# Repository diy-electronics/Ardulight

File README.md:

Ardulight
=========

Ardu(ino)(Ambi)light: An arduino based ambilight controller for WS2801 based digital rgb led pixels.

Example-Video:<br />

Images
------

&nbsp;&nbsp;&nbsp;

Assembly
--------

Assembly instructions including a BOM (bill of materials) can be found [here](../master/pcb).<br />
The pcb has to be soldered by hot air or by reflow due to the qfp package of the atmega32u4.

Wiring
------

For a detailed wiring guide look [here](https://learn.adafruit.com/adalight-diy-ambient-tv-lighting/wiring-1).<br />
The LED-Strip has to be powered from an external power source, using e.g. a connector like [this](https://www.adafruit.com/products/368).<br />
You only have to connect GND, CLK (SCK) and DAT (MOSI).  

Firmware
--------

The firmware can be found [here](../master/firmware/firmware.pde)<br />
You can flash this firmware using an isp-programmer.<br />
Alternatively you can first flash the arduino leonardo bootloader with an isp-programmer and then flash the firmware directly over usb since the ambilight controller is compatible with the arduino leonardo.

Software
--------

The ambilight controller works with [Prismatik from woodenshark](https://github.com/woodenshark/Lightpack/releases/latest) (Alternative download [here](http://lightpack.tv/downloads)).

To fix the systems device name and permissions for Ardulight on linux systems, you can add [the udev rule](98-ardulight.rules) to `/etc/udev/rules.d/`. The device name is then `/dev/ttyARDULIGHT` and is owned by `users (mode 0666)`.

License
-------

<br />This work is licensed under a <a rel="license" href="http://creativecommons.org/licenses/by-sa/4.0/">Creative Commons Attribution-ShareAlike 4.0 International License</a>.<br />
The firmware is licensed under a GNU Lesser General Public, see <http://www.gnu.org/licenses/>.<br />

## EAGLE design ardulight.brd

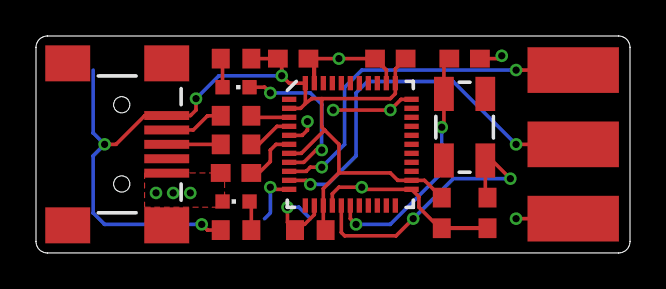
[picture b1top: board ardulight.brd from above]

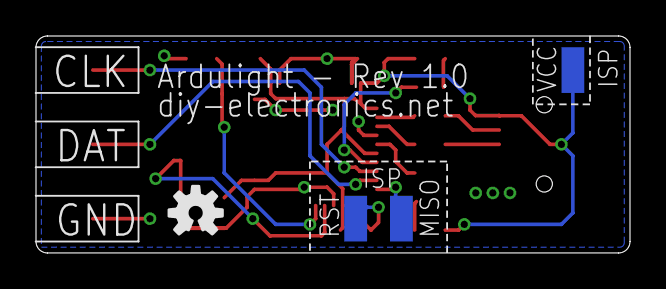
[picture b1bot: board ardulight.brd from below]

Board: 2 copper layers, 33.0 x 12.1 mm, 23 parts (4 on the bottom side), 16 nets.

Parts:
C1, C2, C3: 100n; C0603
C4: 1u; C0603
C5, C6: 18p; C0603
CLK: SMD2,54-5,08
DAT: SMD2,54-5,08
GND: SMD2,54-5,08
JP1: USBSMD; USB-MINIB
MISO: SMD1,27-2,54
PWR: BLUE; CHIPLED_0603
R1: 82R; R0603
R2: 10k; R0603
R3, R4: 22; R0603
R5: 150R; R0603
RST: SMD1,27-2,54
RX: YLW; CHIPLED_0603
U1: ATMEGA32U4QFN2; SPARKFUN-DIGITALIC_QFN-44-NOPAD
U$1: OSHW-LOGO-S
VCC: SMD1,27-2,54
Y1: 16MHz; CRYSTAL-SMD-5X3

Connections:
+5V: C1.2, C2.2, C3.2, JP1.VBUS, R1.2, R2.2, R5.1, U1.2, U1.7, U1.14, U1.24, U1.34, U1.44, VCC.1
GND: C1.1, C2.1, C3.1, C4.1, C5.1, C6.1, GND.1, JP1.GND, PWR.C, U1.5, U1.15, U1.23, U1.33, U1.35, U1.43
MISO: MISO.1, U1.11
MOSI: DAT.1, U1.10
unnamed: C5.2, U1.17, Y1.3
unnamed: C6.2, U1.16, Y1.1
unnamed: R3.1, U1.4
unnamed: C4.2, U1.6
unnamed: RX.C, U1.8
unnamed: R4.1, U1.3
unnamed: JP1.D+, R3.2
unnamed: JP1.D-, R4.2
unnamed: PWR.A, R1.1
unnamed: R5.2, RX.A
RST: R2.1, RST.1, U1.13
SCK: CLK.1, U1.9

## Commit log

2014-03-17 add vcc to isp
2014-03-17 remove
2014-12-04 more information regarding assembly etc
2014-12-04 bom now in pdf
2014-12-04 add images to readme
2014-12-11 add firmware to repo, adjust readme
2014-12-16 add wiring instructions
2015-01-06 added udev rule

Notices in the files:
parts and their libraries:
SparkFun-DigitalIC: Licensing: CC v3.0 Share-Alike You are welcome to use this library for commercial purposes.
